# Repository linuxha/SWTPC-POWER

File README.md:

Note: this power supply is not sufficient to power an original SWTPC but works fine with peripheraltech one's

To edit these files you need diptrace:  https://diptrace.com/diptrace-software/
they have an evaluation version and a free version
from diptrace you can convert the format for eagle the import eagle format into kicad
 
I designed this power supply to power a SWTPC 6800 and a SWTPC 6809 from Peripheraltech
as my SWTPC are an opened set of board I was not willing to use a standard switched power supply
not protected with a risk to touch the main lines..

I used a LAPTOP Power Supply input 100-240v  output 19.5V 6.15A
then I designed a small board with chinese modules to convert 
19.5V to 8V 15V and I inverted the 15V with ICL7662

I planned to use up to 3 ICL7662 but for my SWTPC 6800 only one was necessary

when the SWTPC 6800 was up and running it was drawing roughly 1.5A on 8V

the XL4005 LP2596 module I've chosen are normally able to produce up to 5A  (according to Aliexpress vendor)
[XL4005 LP2596 module](https://fr.aliexpress.com/item/32828277416.html) (French)

the ICL7662 datasheet is in this directory with other files

I tested this power supply with an input varying from 17V to 30V in all cases 8V and 15V were stables
I cut the original Jack connector and Installed a connector suitable with my board

PAY ATTENTION THAT THESE MODULE MUST BE TUNED TO THE CORRECT OUTPUT TENSION
BEFORE BEING CONNECTED TO THE SWTPC

I used a blocking varnish on the potentiometer once tuned to the correct tension

LEDS
- RED    input  present
- GREEN    8v   present
- YELLOW  15v   present
- BLUE   -15V   present

  the resistor for the led are not accurate in the schematics I replaced them by 3.3k to have an indication with the led
  of the presence of tension... with the first resistor values the board was lighten like a christmas tree

CONNECTOR
I used connector easy to find
then I built an adaptor between this connector
and the SWTPC connector so the SWTPC was not modified

the power supply I'm using:
[DTK Laptop Power Supply Charger 19.5V 6.15A 120W](https://www.amazon.fr/DTK-Adaptateur-SyncMaster-dalimentation-Alimentation/dp/B07VL3M8M1/) (Connector: 5.5 x 2.5mm)

[DTK Laptop Power Supply Charger 19.5V 6.15A 120W](https://www.amazon.com/XL4005-DSN5000-Adjustable-Step-Down-Current/dp/B0DGQHQ74B) (2025-07-02)

PAY ATTENTION that this power supply can power one of Peripheraltech SWTPC using very compact memory board
BUT WILL NEVER BE ABLE TO POWER A REAL SWTPC USING A LOT OF MEMORY BOARDS

BUGS:
  the hole in the pcb are not perfectly aligned with the DC DC module.. it is still possible to mount
  the modules by using resistors "tails" for the connection

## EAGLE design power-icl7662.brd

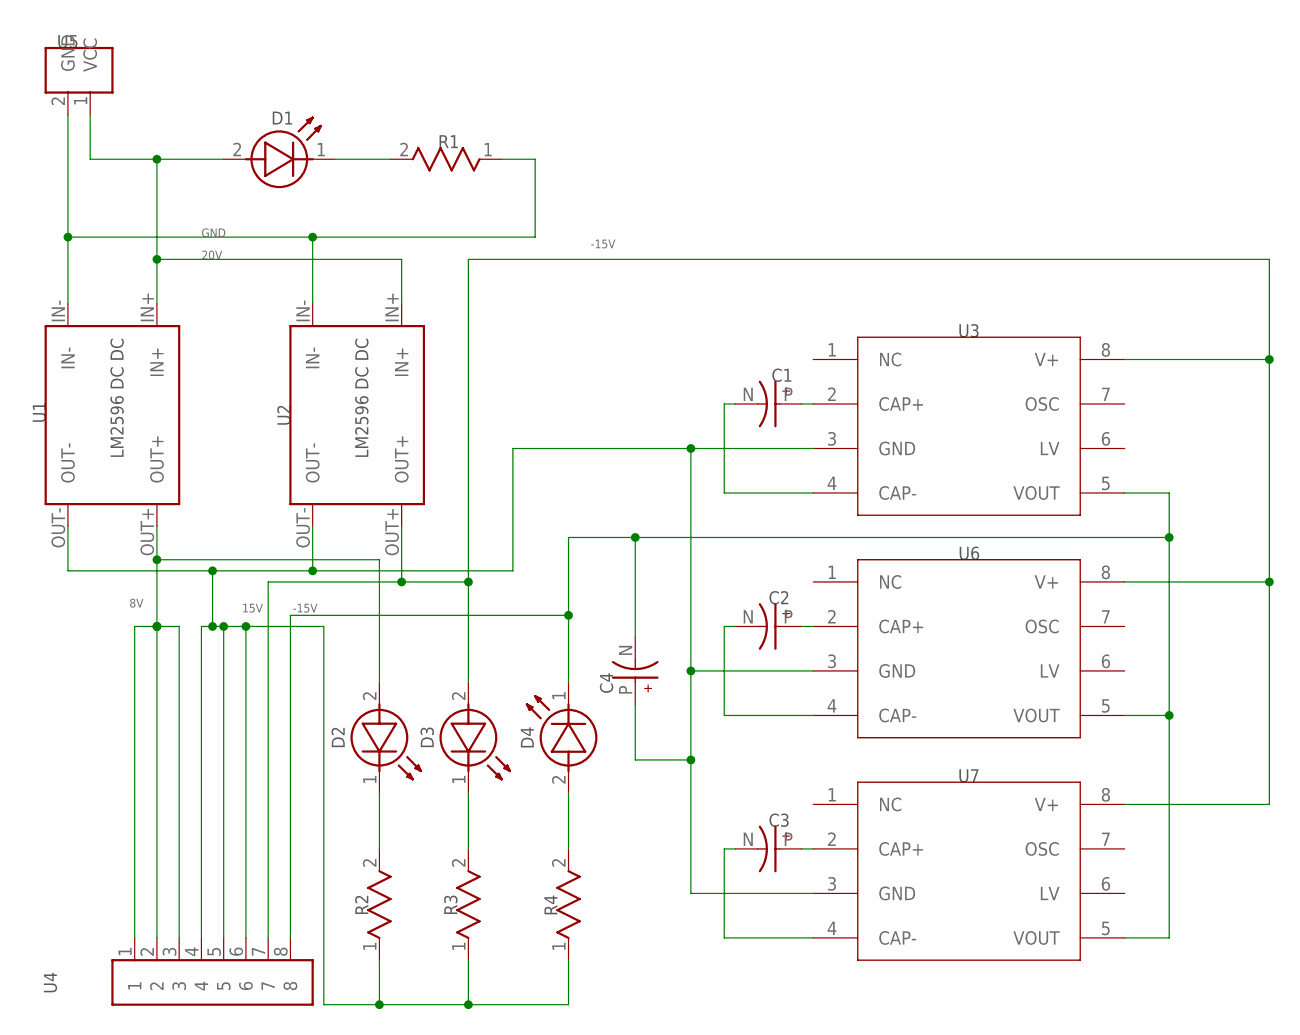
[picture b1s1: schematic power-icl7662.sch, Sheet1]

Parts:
C1, C2: 10µF 25V; CAPPRD250W50D500H1100
C3: 10 µF 25V; CAPPRD250W50D500H1100
C4: 47µF 25V; CAPPRD250W50D500H1100
D1: RED; LED100
D2: GREEN; LED100
D3: YELLOW; LED100
D4: BLEUE; LED100
R1, R2, R3, R4: 2200; RESAD1190W58L750D250
U1, U2: LM2596DCDC
U3, U6, U7: ICL7662-PDIP; DIL-08
U4: 1X8.PTS; PHOENIX-200-8
U5: 1X2.PTS; PHOENIX-200-2

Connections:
8V: D2.2 (A), U1.OUT+, U4.1, U4.2, U4.3
15V: D3.2 (A), U2.OUT+, U3.8 (V+), U4.7, U6.8 (V+), U7.8 (V+)
20V: D1.2 (A), U1.IN+, U2.IN+, U5.1 (VCC)
-15V: C4.N, D4.1 (K), U3.5 (VOUT), U4.8, U6.5 (VOUT), U7.5 (VOUT)
GND: C4.P, R1.1, R2.1, R3.1, R4.1, U1.IN-, U1.OUT-, U2.IN-, U2.OUT-, U3.3 (GND), U4.4, U4.5, U4.6, U5.2 (GND), U6.3 (GND), U7.3 (GND)
Net_5: D1.1 (K), R1.2
Net_6: D2.1 (K), R2.2
Net_7: D3.1 (K), R3.2
Net_8: D4.2 (A), R4.2
Net_9: C1.P, U3.2 (CAP+)
Net_10: C2.P, U6.2 (CAP+)
Net_11: C3.P, U7.2 (CAP+)
Net_12: C1.N, U3.4 (CAP-)
Net_13: C2.N, U6.4 (CAP-)
Net_14: C3.N, U7.4 (CAP-)

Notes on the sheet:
LM2596 DC DC
-15V
15V
20V
GND

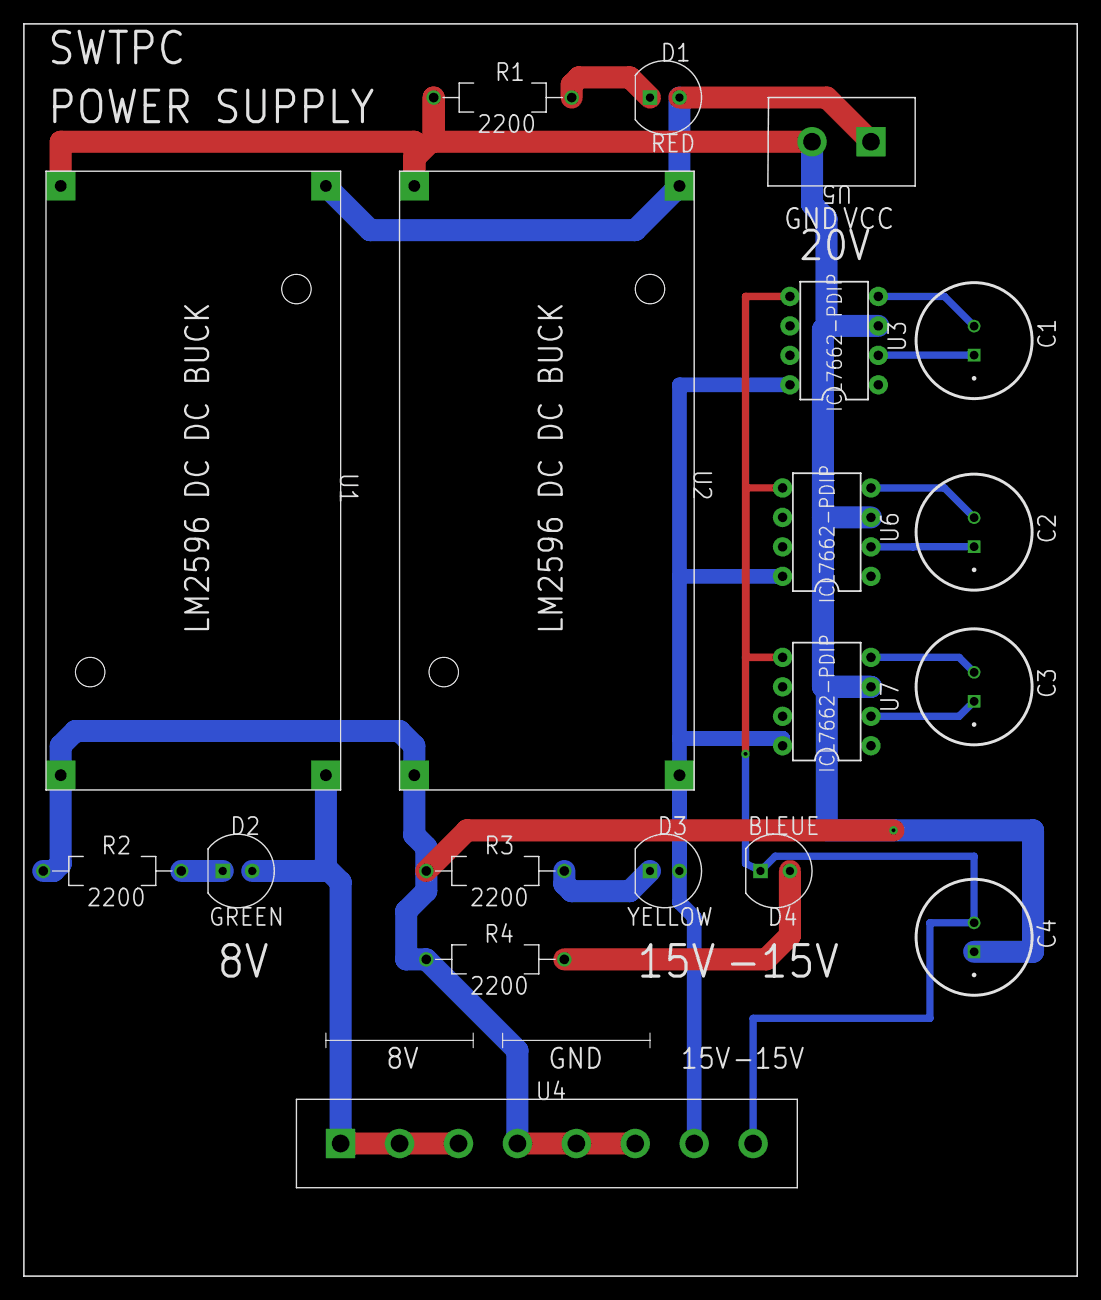
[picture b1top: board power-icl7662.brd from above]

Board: 2 copper layers, 90.8 x 107.9 mm, 19 parts (0 on the bottom side), 15 nets.

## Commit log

2025-07-03 Update README.md
    Updated a few URLs
